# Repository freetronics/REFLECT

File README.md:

# Freetronics Reflect module
http://www.freetronics.com/products/dual-channel-i-r-reflectance-sensor

This sensor incorporates two QRE1113 infra-red reflectance sensors on a single PCB, spaced just the right distance apart to build a line following robot.

The PCB is symmetrical with snap-off holes across the middle, so you can either use it as a pair or snap it in half to have two separate reflectance sensors.

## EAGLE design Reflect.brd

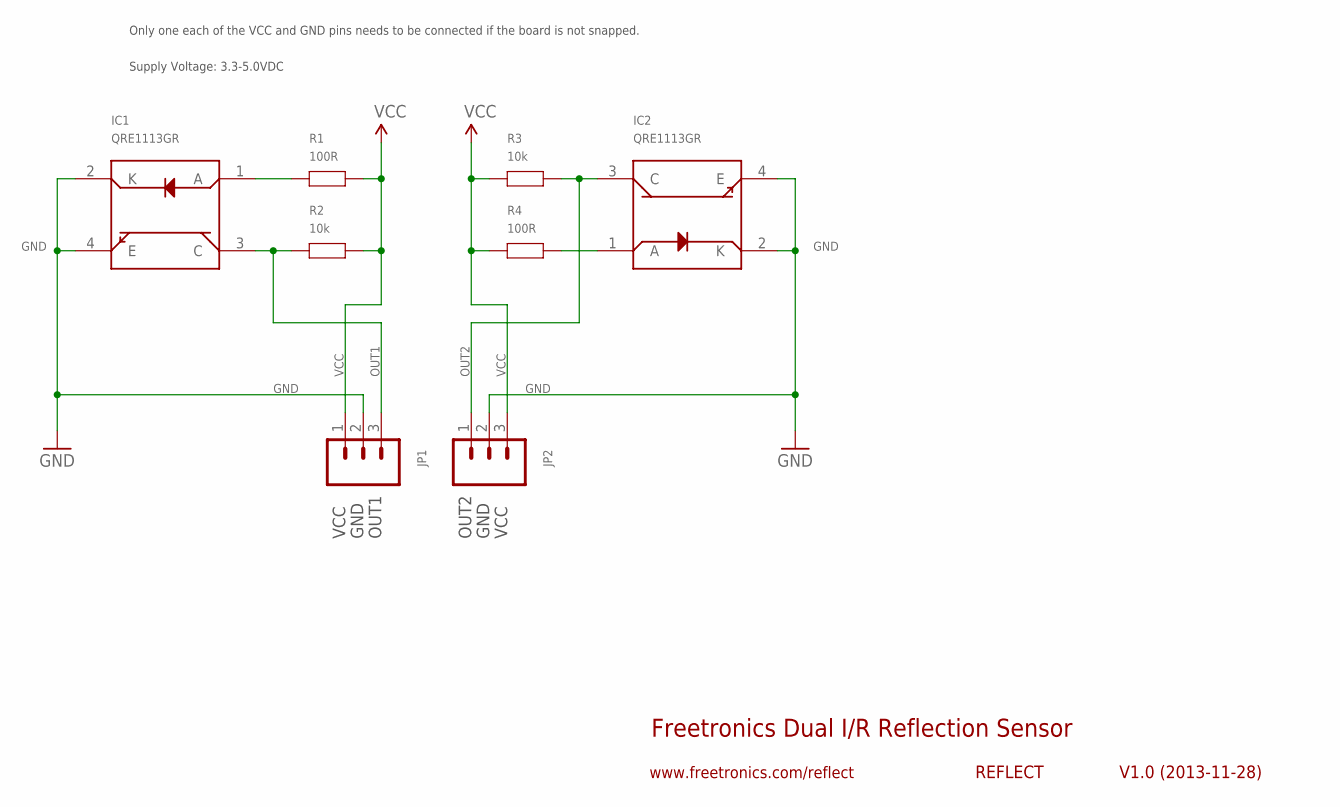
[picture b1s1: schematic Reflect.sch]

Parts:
IC1, IC2: QRE1113GR
JP1, JP2: M03PTH; 1X03
R1, R4: 100R; 0603
R2, R3: 10k; 0603

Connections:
GND: IC1.2 (K), IC1.4 (E), IC2.2 (K), IC2.4 (E), JP1.2, JP2.2
unnamed: IC1.1 (A), R1.1
unnamed: IC2.1 (A), R4.2
OUT1: IC1.3 (C), JP1.3, R2.1
OUT2: IC2.3 (C), JP2.1, R3.2
VCC: JP1.1, JP2.3, R1.2, R2.2, R3.1, R4.1

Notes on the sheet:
Freetronics Dual I/R Reflection Sensor
V1.0 (2013-11-28)
www.freetronics.com/reflect
REFLECT
Supply Voltage: 3.3-5.0VDC
Only one each of the VCC and GND pins needs to be connected if the board is not snapped.
VCC
GND
OUT1
OUT2

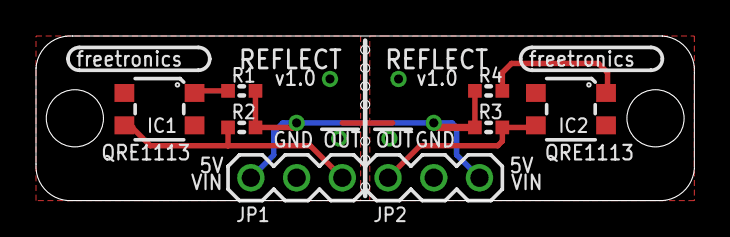
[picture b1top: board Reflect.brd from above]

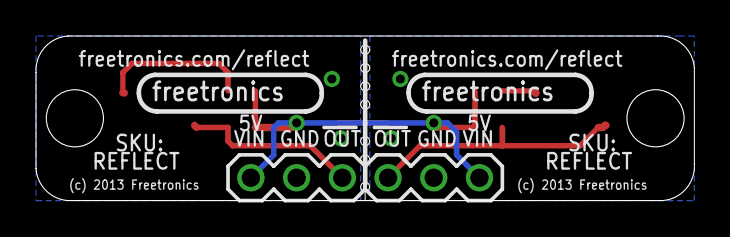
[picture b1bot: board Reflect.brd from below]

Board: 2 copper layers, 36.6 x 9.1 mm, 8 parts (2 on the bottom side), 6 nets.

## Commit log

2013-11-27 Initial import of project.
2013-11-28 Split ground pour into two halves to fix unrouted ground airwire. Added schematic note that although only one VCC pin needs to be connected both ground pins need to be connected if both sensors are u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
2013-11-28 New version with GNDs connected.
2013-11-28 Tweaks to schematic and PCB for v1.0 release
2013-11-28 Changes for v1.0 release: moved headers; changed track size; changed overllay
2014-10-07 Add Readme
2014-10-07 Add schematic PDF

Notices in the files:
Reflect.brd:
(c) 2013 Freetronics
parts and their libraries:
freetronics-original: Licensing: CC v3.0 Share-Alike You are welcome to use this library for commercial purposes.
